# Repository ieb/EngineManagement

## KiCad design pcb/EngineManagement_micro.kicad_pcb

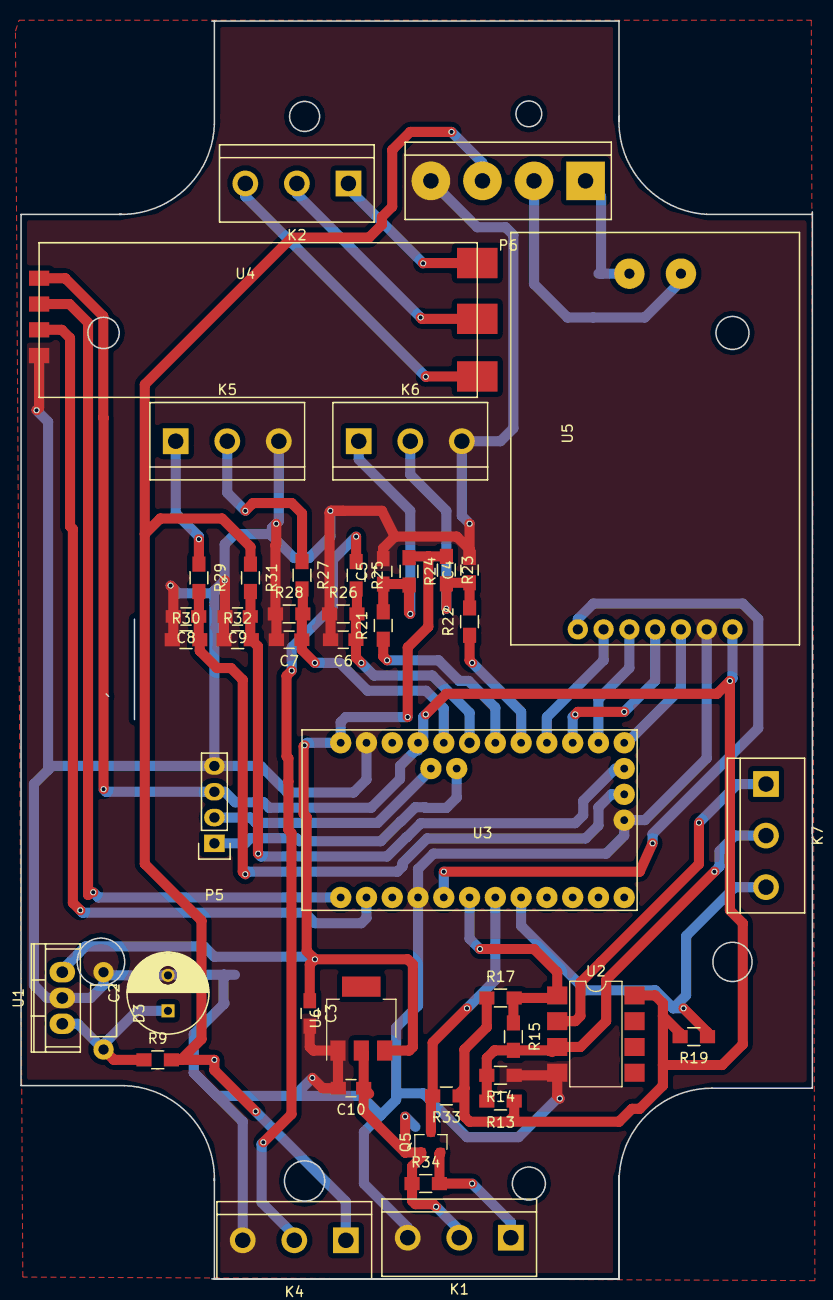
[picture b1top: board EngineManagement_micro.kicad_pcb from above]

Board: 2 copper layers, 78.0 x 124.0 mm, 45 parts (0 on the bottom side), 37 nets.

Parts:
C2: 100uF; C_Radial_D8_L11.5_P3.5
C3, C4, C5: 10nF; C_0805_HandSoldering
C6, C7, C8, C9: 1nF; C_0805_HandSoldering
C10: 100nF; C_0805_HandSoldering
D3: 1N5819; Resistor_Horizontal_RM7mm
K1: 1Wire; bornier3
K2: RS485; bornier3
K4: ToRelays; bornier3
K5: AltBat; bornier3
K6: CoolantFuel; bornier3
K7: FlyOil; bornier3
P5: LCD; Pin_Header_Straight_1x04
P6: J1939; bornier4
Q5: BSS138; SOT-23
R9: 10R; R_0805_HandSoldering
R13, R14, R19, R33, R34: 10K; R_0805_HandSoldering
R15: 22K; R_0805_HandSoldering
R17: 3.3K; R_0805_HandSoldering
R21, R22: 100K; R_0805_HandSoldering
R23, R24: 1K; R_0805_HandSoldering
R25, R27, R29, R31: 1M; R_0805_HandSoldering
R26, R28, R30, R32: 470K; R_0805_HandSoldering
U1: LM7808CT; TO-220
U2: LM358; DIP-8_W7.62mm_SMD
U3: ArdinoMinPro; ArduinoProMini
U4: RS485; RS485Board
U5: MCP2515Shield; MCP2515Board
U6: AMS1117-3v3; SOT-223

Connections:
1-Wire: Q5.3, R33.2, U3.7
3V3: C10.1, K1.2, Q5.1, R34.1, U6.2
5V: P5.3, R13.1, R17.1, R19.2, R33.1, U2.8, U3.21, U4.4, U5.7
8V: C3.1, R23.1, R24.1, U1.3, U3.24, U6.3
AlternatorB+: K5.1, R29.1
BatterySwitchedMCU+: K4.1, P6.3, R9.2, R31.1
CANCS: U3.13, U5.5
CANINT: U3.5, U5.1
CoolantTemp: C5.1, K6.1, R21.2, R24.2
ExcitationMCU: K4.2, R25.1
Flywheel+: K7.2, R13.2, R14.2, R15.2, U2.3
Flywheel-: K7.1, U2.2
FuelLevel+: C4.1, K6.2, R22.2, R23.2
FuelLevel-: C2.2, C3.2, C4.2, C5.2, C6.2, C7.2, C8.2, C9.2, C10.2, D3.1, K1.3, K4.3, K5.3, K6.3, P5.4, P6.4, R14.1, R26.1, R28.1, R30.1, R32.1, U1.2, U2.4, U3.4, U3.23, U3.31, U4.1, U5.6, U6.1
MISI: U3.14, U5.3
MISO: U3.15, U5.4
unnamed: C2.1, D3.2, R9.1, U1.1
unnamed: C6.1, R25.2, R26.2, U3.19
unnamed: C7.1, R27.2, R28.2, U3.20
unnamed: C8.1, R29.2, R30.2, U3.A6
unnamed: C9.1, R31.2, R32.2, U3.A7
unnamed: K1.1, Q5.2, R34.2
unnamed: K2.1, U4.5
unnamed: K2.2, U4.6
unnamed: K2.3, U4.7
unnamed: P5.1, U3.A4
unnamed: P5.2, U3.A5
unnamed: P6.1, U5.8
unnamed: P6.2, U5.9
unnamed: R15.1, R17.2, U2.1, U3.6
unnamed: R21.1, U3.18
unnamed: R22.1, U3.17
OilPressure: K7.3, R19.1, U3.8
RX: U3.2, U4.2
SCK: U3.16, U5.2
ServiceBattery+: K5.2, R27.1
TX: U3.1, U4.3
